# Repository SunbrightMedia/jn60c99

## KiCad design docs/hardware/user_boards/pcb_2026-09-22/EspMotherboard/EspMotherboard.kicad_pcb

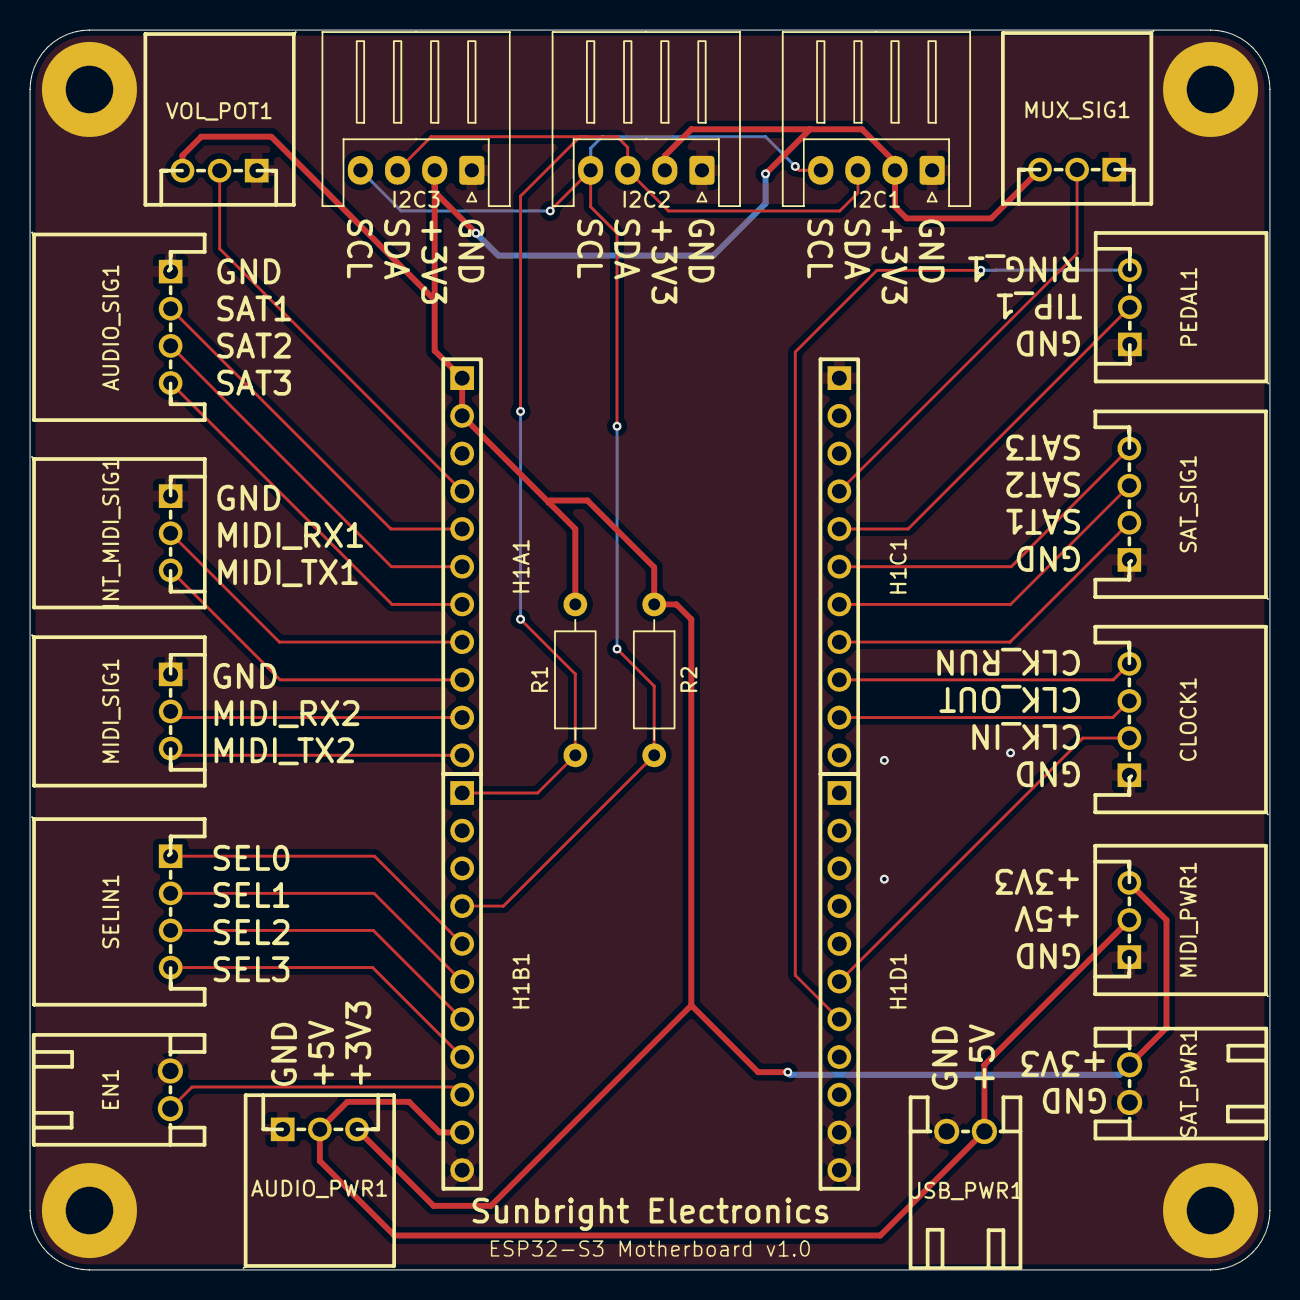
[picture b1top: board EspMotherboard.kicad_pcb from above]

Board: 2 copper layers, 83.5 x 83.5 mm, 27 parts (0 on the bottom side), 27 nets.

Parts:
AUDIO_PWR1: AUDIO_PWR; CONN-TH_S3B-XH-A-LF-SN
AUDIO_SIG1: AUDIO_SIG; CONN-TH_S4B-XH-A-LF-SN
CLOCK1: CLOCK_SYNC; CONN-TH_S4B-XH-A-LF-SN
EN1: BACKUP_MUX_EN; CONN-TH_S2B-XH-A-LF-SN
H1, H2, H3, H4: MountingHole_Pad; MountingHole_3.2mm_M3_Pad
H1A1, H1B1, H1C1, H1D1: ESP32-S3 CONN; HDR-TH_11P-P2.54-V-F-1
I2C1: I2C_1; JST_XH_S4B-XH-A_1x04_P2.50mm_Horizontal
I2C2: I2C_2; JST_XH_S4B-XH-A_1x04_P2.50mm_Horizontal
I2C3: I2C_3_STEMMA; JST_XH_S4B-XH-A_1x04_P2.50mm_Horizontal
INT_MIDI_SIG1: INT_MIDI_SIG; CONN-TH_S3B-XH-A-LF-SN
MIDI_PWR1: MIDI_PWR; CONN-TH_S3B-XH-A-LF-SN
MIDI_SIG1: MIDI_SIG; CONN-TH_S3B-XH-A-LF-SN
MUX_SIG1: MUX_SIG; CONN-TH_S3B-XH-A-LF-SN
PEDAL1: FOOTPEDAL_1; CONN-TH_S3B-XH-A-LF-SN
R1, R2: 4.7k; R_Axial_DIN0207_L6.3mm_D2.5mm_P10.16mm_Horizontal
SAT_PWR1: SAT_PWR; CONN-TH_S2B-XH-A-LF-SN
SAT_SIG1: SAT_SIG; CONN-TH_S4B-XH-A-LF-SN
SELIN1: BACKUP_MUX_SEL; CONN-TH_S4B-XH-A-LF-SN
USB_PWR1: USB_PWR; CONN-TH_S2B-XH-A-LF-SN
VOL_POT1: VOL_POT; CONN-TH_S3B-XH-A-LF-SN

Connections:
+3V3: AUDIO_PWR1.3, H1A1.1, H1A1.2, I2C1.2, I2C2.2, I2C3.2, MIDI_PWR1.3, MUX_SIG1.3, R1.2, R2.1, SAT_PWR1.2, VOL_POT1.3
+5V: AUDIO_PWR1.2, H1B1.10, MIDI_PWR1.2, USB_PWR1.2
CLK_IN: CLOCK1.2, H1D1.6
CLK_OUT: CLOCK1.3, H1C1.10
GND: AUDIO_PWR1.1, AUDIO_SIG1.1, CLOCK1.1, EN1.1, H1.1 (1_1), H1B1.11, H1C1.1, H1D1.10, H1D1.11, H2.1 (1_1), H3.1 (1_1), H4.1 (1_1), I2C1.1, I2C2.1, I2C3.1, INT_MIDI_SIG1.1, MIDI_PWR1.1, MIDI_SIG1.1, MUX_SIG1.1, PEDAL1.1, SAT_PWR1.1, SAT_SIG1.1, USB_PWR1.1, VOL_POT1.1
I2S_BCK_RS: AUDIO_SIG1.2, H1A1.5
I2S_SD_RS: AUDIO_SIG1.4, H1A1.7
I2S_WS_RS: AUDIO_SIG1.3, H1A1.6
INT_MIDI_RX: H1A1.8, INT_MIDI_SIG1.2
INT_MIDI_TX: H1A1.9, INT_MIDI_SIG1.3
MIDI_RX: H1A1.10, MIDI_SIG1.2
MIDI_TX: H1A1.11, MIDI_SIG1.3
MUX_IN: H1C1.4, MUX_SIG1.2
RING_1: H1D1.7, PEDAL1.3
RUN: CLOCK1.4, H1C1.9
SAT1: H1C1.8, SAT_SIG1.2
SAT2: H1C1.7, SAT_SIG1.3
SAT3: H1C1.6, SAT_SIG1.4
SCL: H1B1.4, I2C1.4, I2C2.4, I2C3.4, R2.2
SDA: H1B1.1, I2C1.3, I2C2.3, I2C3.3, R1.1
SEL0: H1B1.5, SELIN1.1
SEL1: H1B1.6, SELIN1.2
SEL2: H1B1.7, SELIN1.3
SEL3: H1B1.8, SELIN1.4
SPARE_EN: EN1.2, H1B1.9
TIP_1: H1C1.5, PEDAL1.2
VOL_POT: H1A1.4, VOL_POT1.2

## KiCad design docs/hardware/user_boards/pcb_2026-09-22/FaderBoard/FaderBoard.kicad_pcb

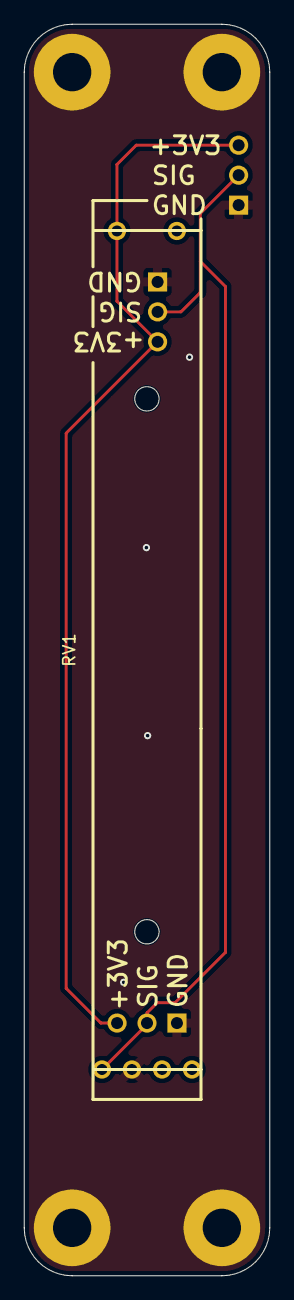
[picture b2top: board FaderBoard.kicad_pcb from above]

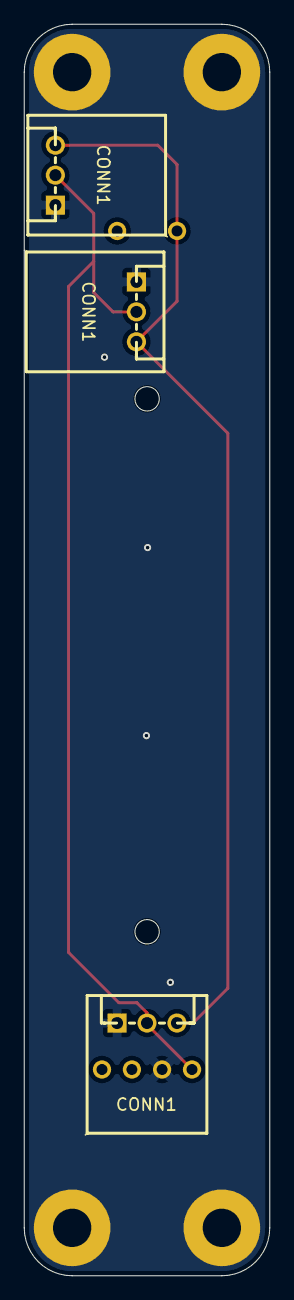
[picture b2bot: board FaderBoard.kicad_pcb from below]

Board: 2 copper layers, 20.5 x 104.5 mm, 8 parts (3 on the bottom side), 3 nets.

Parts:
CONN1, CONN1#2, CONN1#3: SIGNAL; CONN-TH_S3B-XH-A-LF-SN
H1, H2, H3, H4: MountingHole_Pad; MountingHole_3.2mm_M3_Pad
RV1: Fader_Dual_75mm; Fader_Slide_Dual_75mm_60mmTravel_B103

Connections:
+3V3: CONN1.3, CONN1#2.3, CONN1#3.3, RV1.3A (A_end2)
GND: CONN1.1, CONN1#2.1, CONN1#3.1, H1.1 (1_1), H2.1 (1_1), H3.1 (1_1), H4.1 (1_1), RV1.1A (A_end1)
SIG: CONN1.2, CONN1#2.2, CONN1#3.2, RV1.2A (A_wiper)

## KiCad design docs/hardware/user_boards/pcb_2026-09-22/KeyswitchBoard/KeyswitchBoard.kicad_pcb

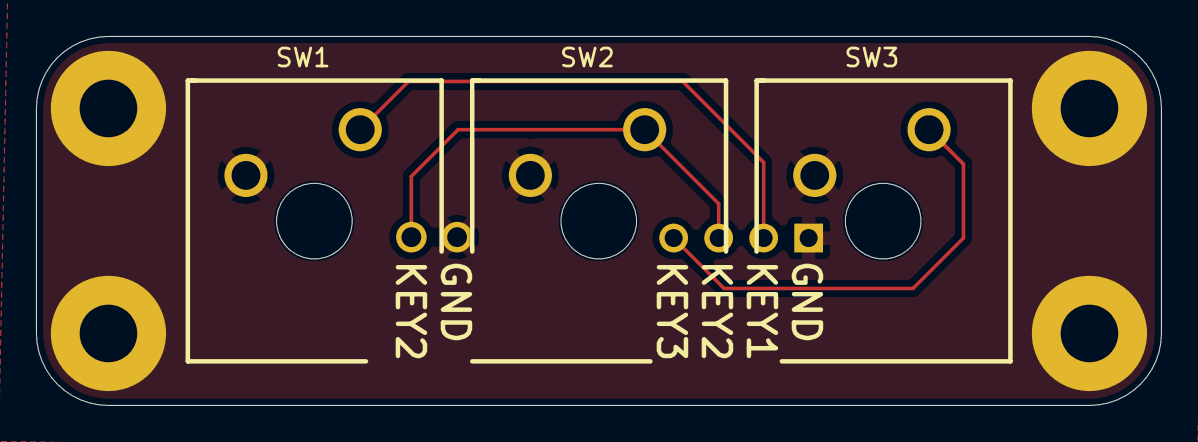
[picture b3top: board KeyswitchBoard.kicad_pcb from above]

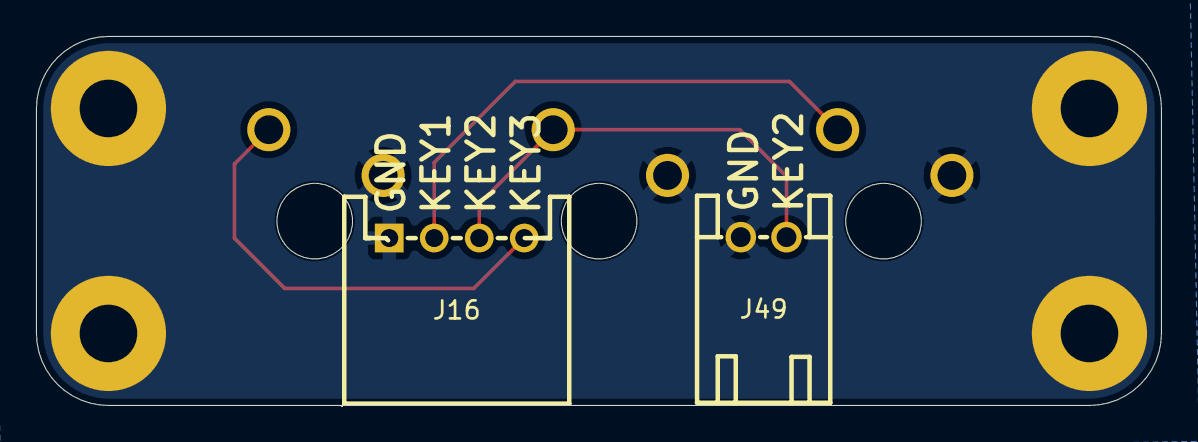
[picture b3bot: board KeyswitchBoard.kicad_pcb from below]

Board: 2 copper layers, 62.5 x 20.5 mm, 9 parts (2 on the bottom side), 4 nets.

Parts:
H1, H2, H3, H4: MountingHole_Pad; MountingHole_3.2mm_M3_Pad
J16: GROUP1; CONN-TH_S4B-XH-A-LF-SN
J49: JST-XH PWR; CONN-TH_S2B-XH-A-LF-SN
SW1, SW2, SW3: KEYSWITCH; KEY-TH_CPG1511_15.75

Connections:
GND: H1.1 (1_1), H2.1 (1_1), H3.1 (1_1), H4.1 (1_1), J16.1, J49.1, SW1.1, SW2.1, SW3.1
KEY1: J16.2, SW1.2
KEY2: J16.3, J49.2, SW2.2
KEY3: J16.4, SW3.2

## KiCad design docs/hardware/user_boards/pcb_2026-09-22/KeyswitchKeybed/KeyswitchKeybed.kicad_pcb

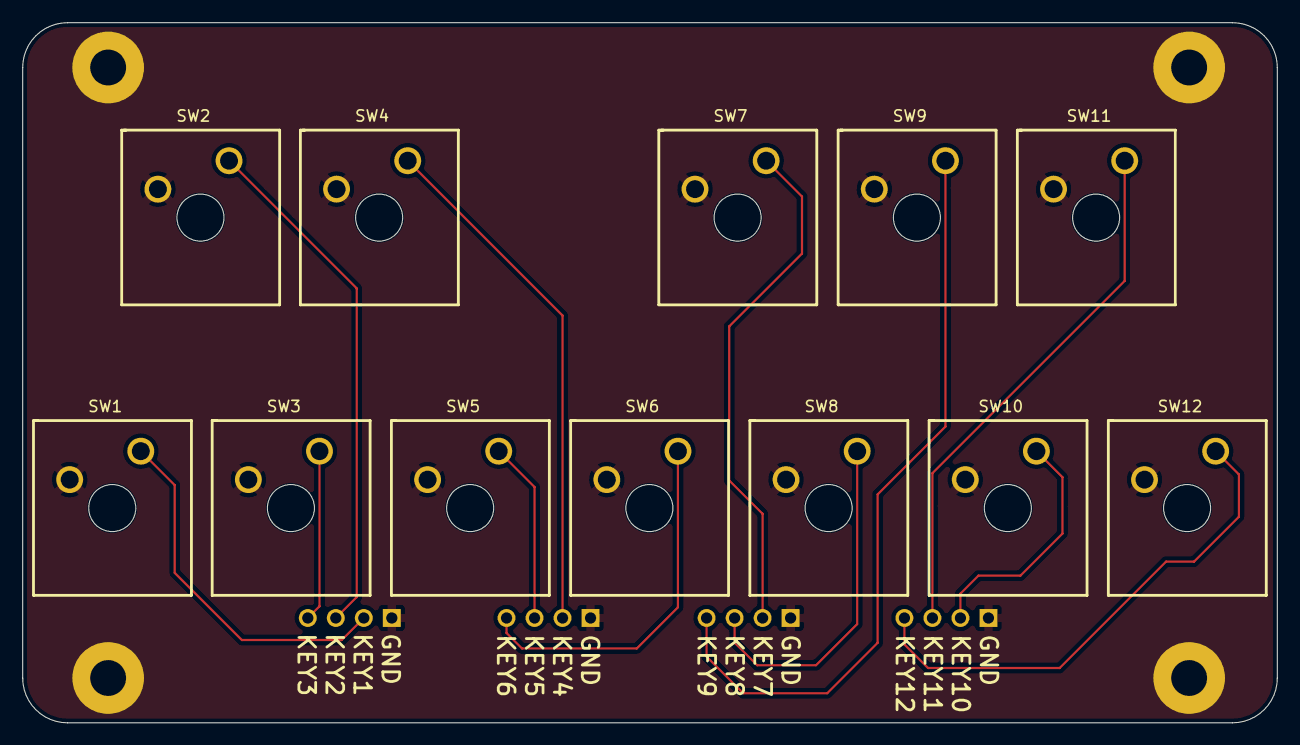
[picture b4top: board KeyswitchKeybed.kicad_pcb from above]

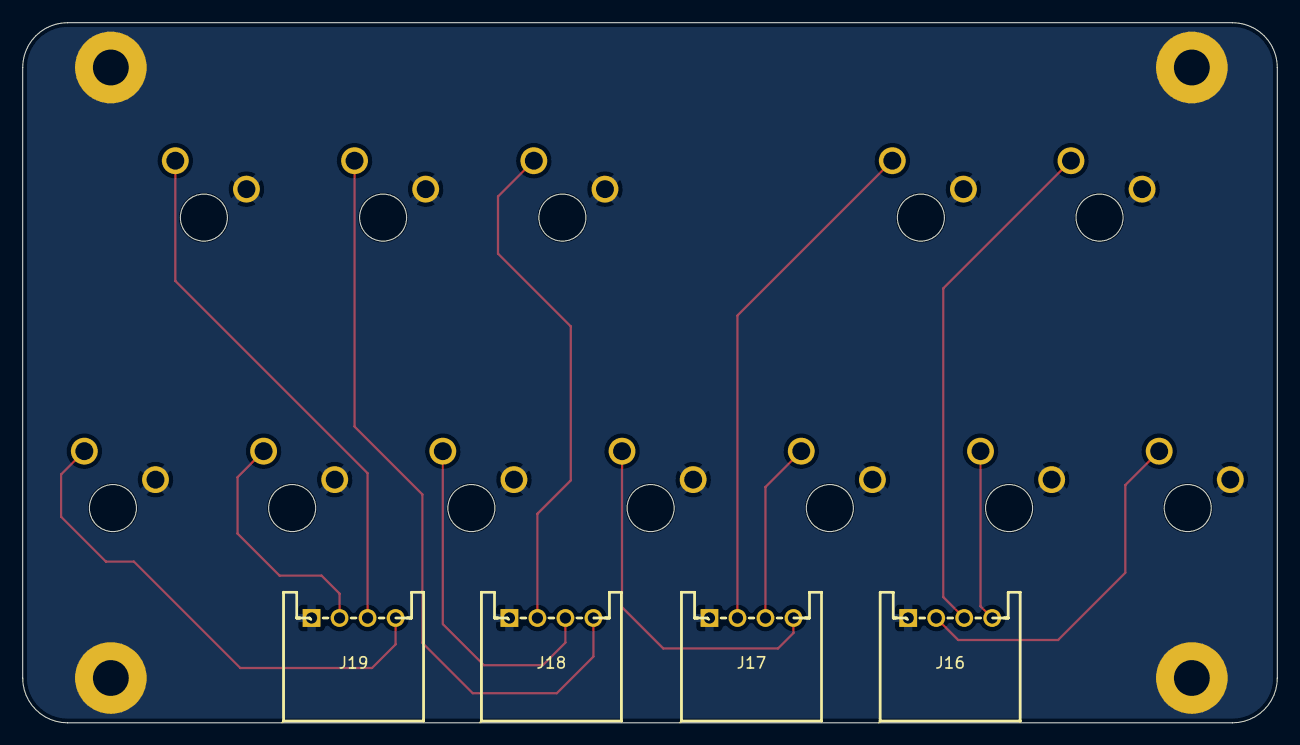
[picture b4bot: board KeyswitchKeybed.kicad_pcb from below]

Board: 2 copper layers, 112.0 x 62.5 mm, 20 parts (4 on the bottom side), 13 nets.

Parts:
H1, H2, H3, H4: MountingHole_Pad; MountingHole_3.2mm_M3_Pad
J16: GROUP1; CONN-TH_S4B-XH-A-LF-SN
J17: GROUP2; CONN-TH_S4B-XH-A-LF-SN
J18: GROUP3; CONN-TH_S4B-XH-A-LF-SN
J19: GROUP4; CONN-TH_S4B-XH-A-LF-SN
SW1, SW2, SW3, SW4, SW5, SW6, SW7, SW8, SW9, SW10, SW11, SW12: KEYSWITCH; KEY-TH_CPG1511_15.75

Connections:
GND: H1.1 (1_1), H2.1 (1_1), H3.1 (1_1), H4.1 (1_1), J16.1, J17.1, J18.1, J19.1, SW1.1, SW2.1, SW3.1, SW4.1, SW5.1, SW6.1, SW7.1, SW8.1, SW9.1, SW10.1, SW11.1, SW12.1
KEY1: J16.2, SW1.2
KEY2: J16.3, SW2.2
KEY3: J16.4, SW3.2
KEY4: J17.2, SW4.2
KEY5: J17.3, SW5.2
KEY6: J17.4, SW6.2
KEY7: J18.2, SW7.2
KEY8: J18.3, SW8.2
KEY9: J18.4, SW9.2
KEY10: J19.2, SW10.2
KEY11: J19.3, SW11.2
KEY12: J19.4, SW12.2

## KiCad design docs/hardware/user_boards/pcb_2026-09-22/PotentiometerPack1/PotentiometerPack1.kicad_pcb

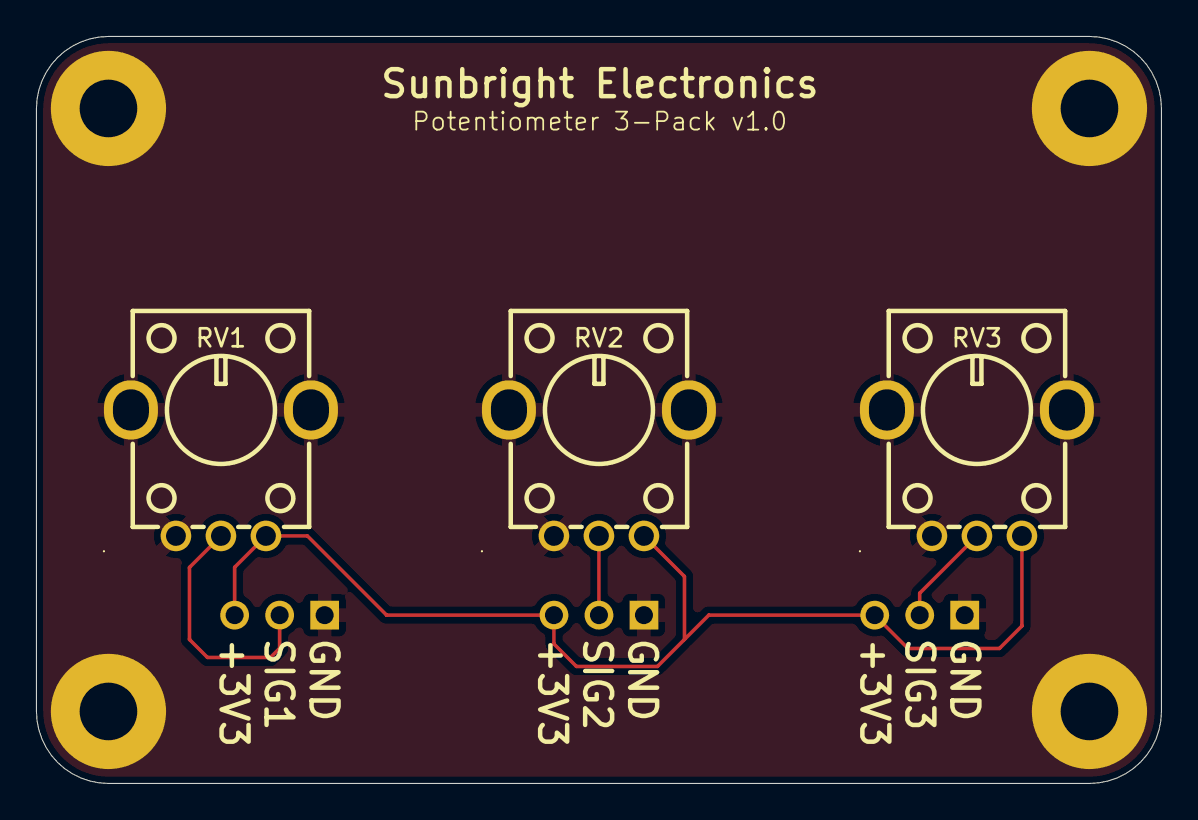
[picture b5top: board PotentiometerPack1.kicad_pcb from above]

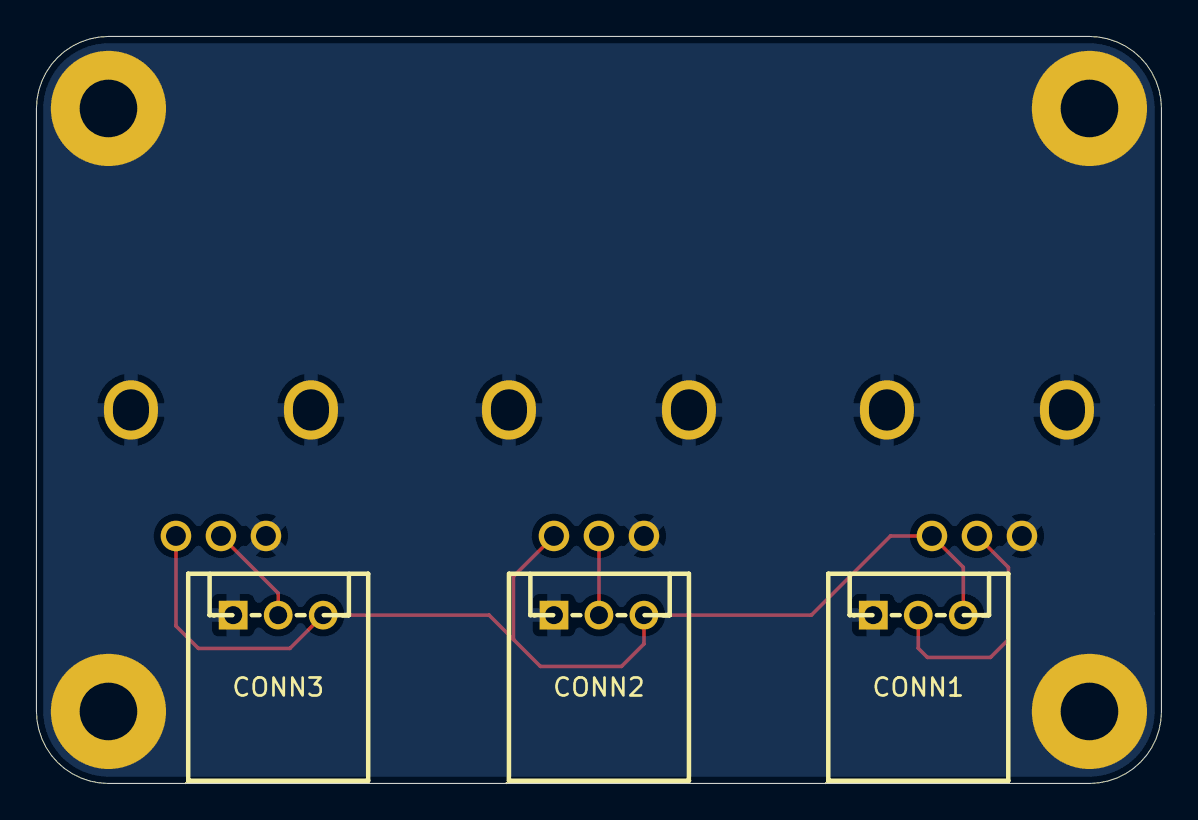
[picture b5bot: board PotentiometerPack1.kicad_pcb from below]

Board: 2 copper layers, 62.5 x 41.5 mm, 10 parts (3 on the bottom side), 5 nets.

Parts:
CONN1, CONN2, CONN3: SIGNAL; CONN-TH_S3B-XH-A-LF-SN
H1, H2, H3, H4: MountingHole_Pad; MountingHole_3.2mm_M3_Pad
RV1, RV2, RV3: RK09K1130A70; RES-TH_RK09K1130A70

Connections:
+3V3: CONN1.3, CONN2.3, CONN3.3, RV1.3, RV2.3, RV3.3
GND: CONN1.1, CONN2.1, CONN3.1, H1.1 (1_1), H2.1 (1_1), H3.1 (1_1), H4.1 (1_1), RV1.1, RV1.4 (EH), RV1.5 (EH), RV2.1, RV2.4 (EH), RV2.5 (EH), RV3.1, RV3.4 (EH), RV3.5 (EH)
SIG1: CONN1.2, RV1.2
SIG2: CONN2.2, RV2.2
SIG3: CONN3.2, RV3.2

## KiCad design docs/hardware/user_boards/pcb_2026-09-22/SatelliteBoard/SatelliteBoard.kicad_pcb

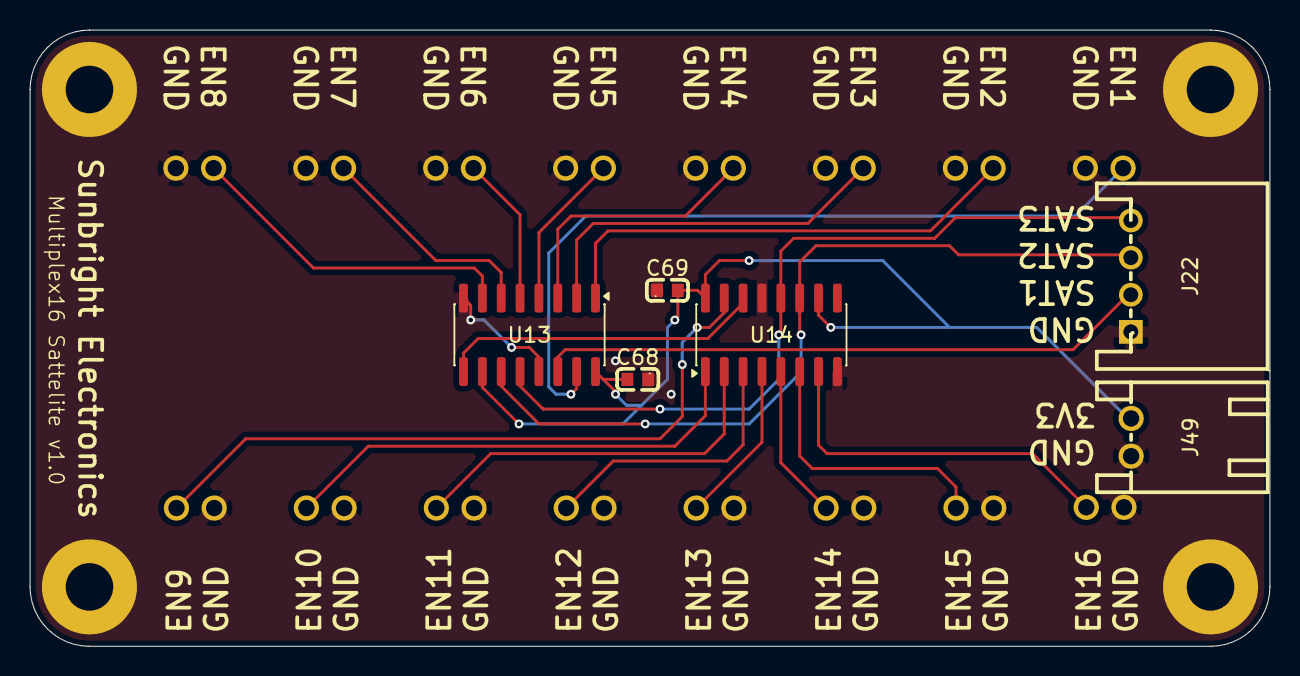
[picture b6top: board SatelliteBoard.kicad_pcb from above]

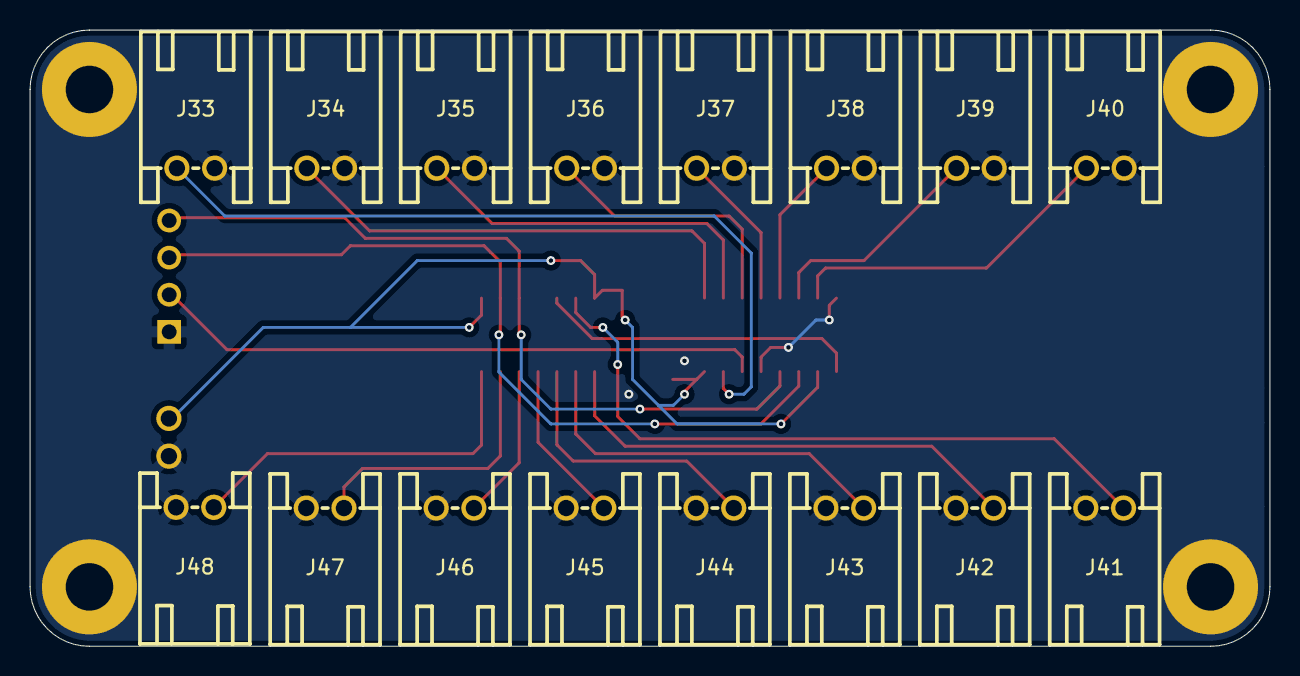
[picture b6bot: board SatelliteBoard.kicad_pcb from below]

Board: 2 copper layers, 83.5 x 41.5 mm, 26 parts (16 on the bottom side), 22 nets.

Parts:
C68, C69: CC0603KRX7R9BB104; C0603
H1, H2, H3, H4: MountingHole_Pad; MountingHole_3.2mm_M3_Pad
J22: JST-XH CONT; CONN-TH_S4B-XH-A-LF-SN
J33: JST-XH MUX EN1; CONN-TH_S2B-XH-A-LF-SN
J34: JST-XH MUX EN2; CONN-TH_S2B-XH-A-LF-SN
J35: JST-XH MUX EN3; CONN-TH_S2B-XH-A-LF-SN
J36: JST-XH MUX EN4; CONN-TH_S2B-XH-A-LF-SN
J37: JST-XH MUX EN5; CONN-TH_S2B-XH-A-LF-SN
J38: JST-XH MUX EN6; CONN-TH_S2B-XH-A-LF-SN
J39: JST-XH MUX EN7; CONN-TH_S2B-XH-A-LF-SN
J40: JST-XH MUX EN8; CONN-TH_S2B-XH-A-LF-SN
J41: JST-XH MUX EN9; CONN-TH_S2B-XH-A-LF-SN
J42: JST-XH MUX EN10; CONN-TH_S2B-XH-A-LF-SN
J43: JST-XH MUX EN11; CONN-TH_S2B-XH-A-LF-SN
J44: JST-XH MUX EN12; CONN-TH_S2B-XH-A-LF-SN
J45: JST-XH MUX EN13; CONN-TH_S2B-XH-A-LF-SN
J46: JST-XH MUX EN14; CONN-TH_S2B-XH-A-LF-SN
J47: JST-XH MUX EN15; CONN-TH_S2B-XH-A-LF-SN
J48: JST-XH MUX EN16; CONN-TH_S2B-XH-A-LF-SN
J49: JST-XH PWR; CONN-TH_S2B-XH-A-LF-SN
U13, U14: SN74HC595DR; SOIC-16_3.9x9.9mm_P1.27mm

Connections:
3V3_ESP1: C68.2, C69.2, J49.2, U13.10 (~MR), U13.16 (VCC), U14.10 (~MR), U14.16 (VCC)
EXT_2: J22.2, U13.14 (DS)
EXT_3: J22.3, U13.11 (SHCP), U14.11 (SHCP)
EXT_4: J22.4, U13.12 (STCP), U14.12 (STCP)
GND: C68.1, C69.1, H1.1 (1_1), H2.1 (1_1), H3.1 (1_1), H4.1 (1_1), J22.1, J33.1, J34.1, J35.1, J36.1, J37.1, J38.1, J39.1, J40.1, J41.1, J42.1, J43.1, J44.1, J45.1, J46.1, J47.1, J48.1, J49.1, U13.8 (GND), U13.13 (~OE), U14.8 (GND), U14.13 (~OE)
MCLINK: U13.9 (QH'), U14.14 (DS)
MUX_EN_1: J33.2, U13.15 (QA)
MUX_EN_2: J34.2, U13.1 (QB)
MUX_EN_3: J35.2, U13.2 (QC)
MUX_EN_4: J36.2, U13.3 (QD)
MUX_EN_5: J37.2, U13.4 (QE)
MUX_EN_6: J38.2, U13.5 (QF)
MUX_EN_7: J39.2, U13.6 (QG)
MUX_EN_8: J40.2, U13.7 (QH)
MUX_EN_9: J41.2, U14.15 (QA)
MUX_EN_10: J42.2, U14.1 (QB)
MUX_EN_11: J43.2, U14.2 (QC)
MUX_EN_12: J44.2, U14.3 (QD)
MUX_EN_13: J45.2, U14.4 (QE)
MUX_EN_14: J46.2, U14.5 (QF)
MUX_EN_15: J47.2, U14.6 (QG)
MUX_EN_16: J48.2, U14.7 (QH)
